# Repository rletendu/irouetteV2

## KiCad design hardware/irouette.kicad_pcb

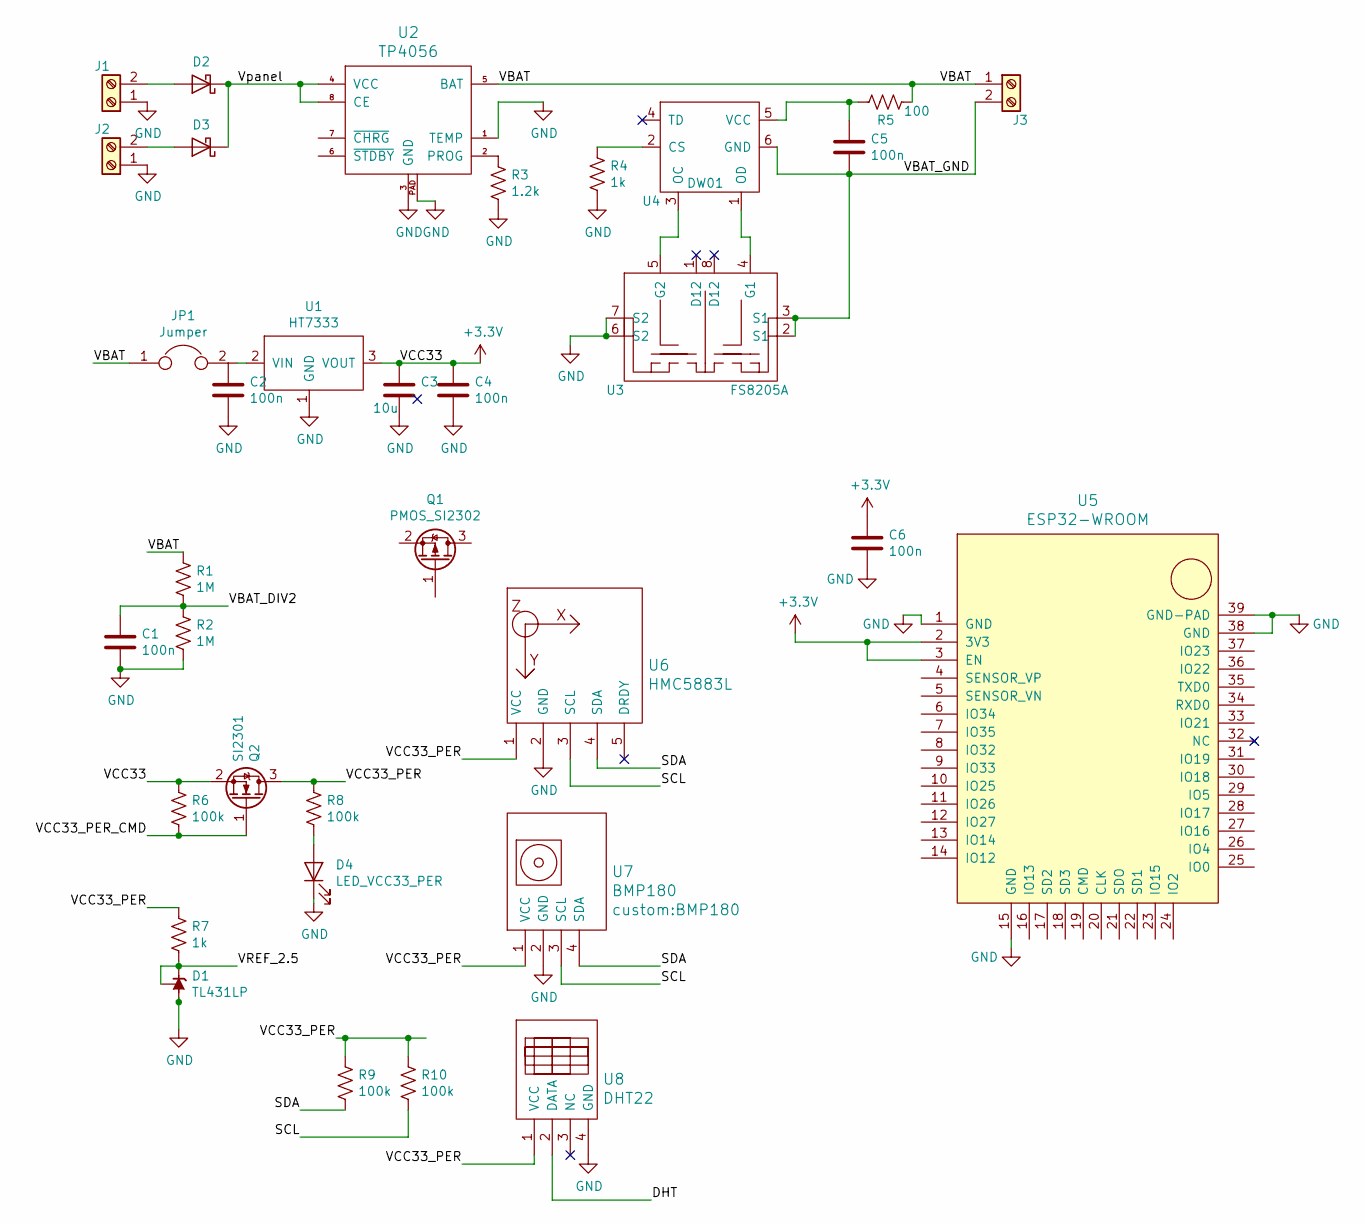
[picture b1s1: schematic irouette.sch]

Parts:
C1, C2, C4, C5, C6: 100n; C_0805_2012Metric_Pad1.15x1.40mm_HandSolder
C3: 10u; CP_Elec_3x5.4
D1: TL431LP; SOT-23
D2, D3: 1N5818; D_SMA_Handsoldering
D4: LED_VCC33_PER; LED_0805_2012Metric
J1, J2, J3: Screw_Terminal_01x02; TerminalBlock_bornier-2_P5.08mm
JP1: Jumper; PinHeader_1x02_P2.54mm_Vertical
Q1: PMOS_SI2302; SOT-23
Q2: SI2301; SOT-23
R1, R2: 1M; R_0805_2012Metric_Pad1.15x1.40mm_HandSolder
R3: 1.2k; R_0805_2012Metric_Pad1.15x1.40mm_HandSolder
R4, R7: 1k; R_0805_2012Metric_Pad1.15x1.40mm_HandSolder
R5: 100; R_0805_2012Metric_Pad1.15x1.40mm_HandSolder
R6, R8, R9, R10: 100k; R_0805_2012Metric_Pad1.15x1.40mm_HandSolder
U1: HT7333; SOT-89-3_Handsoldering
U2: TP4056; HSOP-8-1EP_3.9x4.9mm_P1.27mm_EP2.41x3.1mm
U3: FS8205A; TSSOP-8_4.4x3mm_P0.65mm
U4: DW01; SOT-23-6_Handsoldering
U5: ESP32-WROOM; esp32_wroom
U6: HMC5883L
U7: BMP180
U8: DHT22

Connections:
+3V3: C3.1, C4.1, C6.1, Q2.2 (S), R6.1, U1.3 (VOUT), U5.2 (3V3), U5.3 (EN)
/SCL: R10.2, U6.3 (SCL), U7.3 (SCL)
/SDA: R9.2, U6.4 (SDA), U7.4 (SDA)
/VBAT: J3.1, JP1.1, R1.1, R5.1, U2.5 (BAT)
/VBAT_DIV2: C1.1, R1.2, R2.1
/VBAT_GND: C5.2, J3.2, U3.2 (S1), U3.3 (S1), U4.6 (GND)
/VCC33_PER: Q2.3 (D), R7.1, R8.1, R9.1, R10.1, U6.1 (VCC), U7.1 (VCC), U8.1 (VCC)
/VCC33_PER_CMD: Q2.1 (G), R6.2
/VREF_2.5: D1.1 (REF), D1.3 (K), R7.2
/Vpanel: D2.1 (K), D3.1 (K), U2.4 (VCC), U2.8 (CE)
GND: C1.2, C2.2, C3.2, C4.2, C6.2, D1.2 (A), D4.1 (K), J1.1, J2.1, R2.2, R3.2, R4.2, U1.1 (GND), U2.1 (TEMP), U2.3 (GND), U2.PAD, U3.6 (S2), U3.7 (S2), U5.1 (GND), U5.15 (GND), U5.38 (GND), U5.39 (GND-PAD), U6.2 (GND), U7.2 (GND), U8.4 (GND)
unnamed: C5.1, R5.2, U4.5 (VCC)
unnamed: D2.2 (A), J1.2
unnamed: D3.2 (A), J2.2
unnamed: D4.2 (A), R8.2
unnamed: JP1.2, U1.2 (VIN)
unnamed: R3.1, U2.2 (PROG)
unnamed: R4.1, U4.2 (CS)
unnamed: U3.4 (G1), U4.1 (OD)
unnamed: U3.5 (G2), U4.3 (OC)

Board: 2 copper layers, 32 parts (0 on the bottom side), 20 nets, no tracks yet.

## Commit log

2018-12-04 Initial
2018-12-05 Update 3D path
2018-12-07 Updated libs
2018-12-07 Updated 3D model for wroom32
2018-12-10 Update schematic with vcc peripheral generation
2018-12-11 Changed LED
2018-12-12 Adding sensoes
2018-12-14 Adding attempt to create free cad module generator
